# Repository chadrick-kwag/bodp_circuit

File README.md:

# bodp_circuit
battery over discharge protection circuit project.
A blog post explaining the design background and measurement procedure and results is [here](https://kwagjj.wordpress.com/2016/10/09/battery-overdischarge-protection-circuit/). Please check this post to get a glimpse of what this circuit can do.

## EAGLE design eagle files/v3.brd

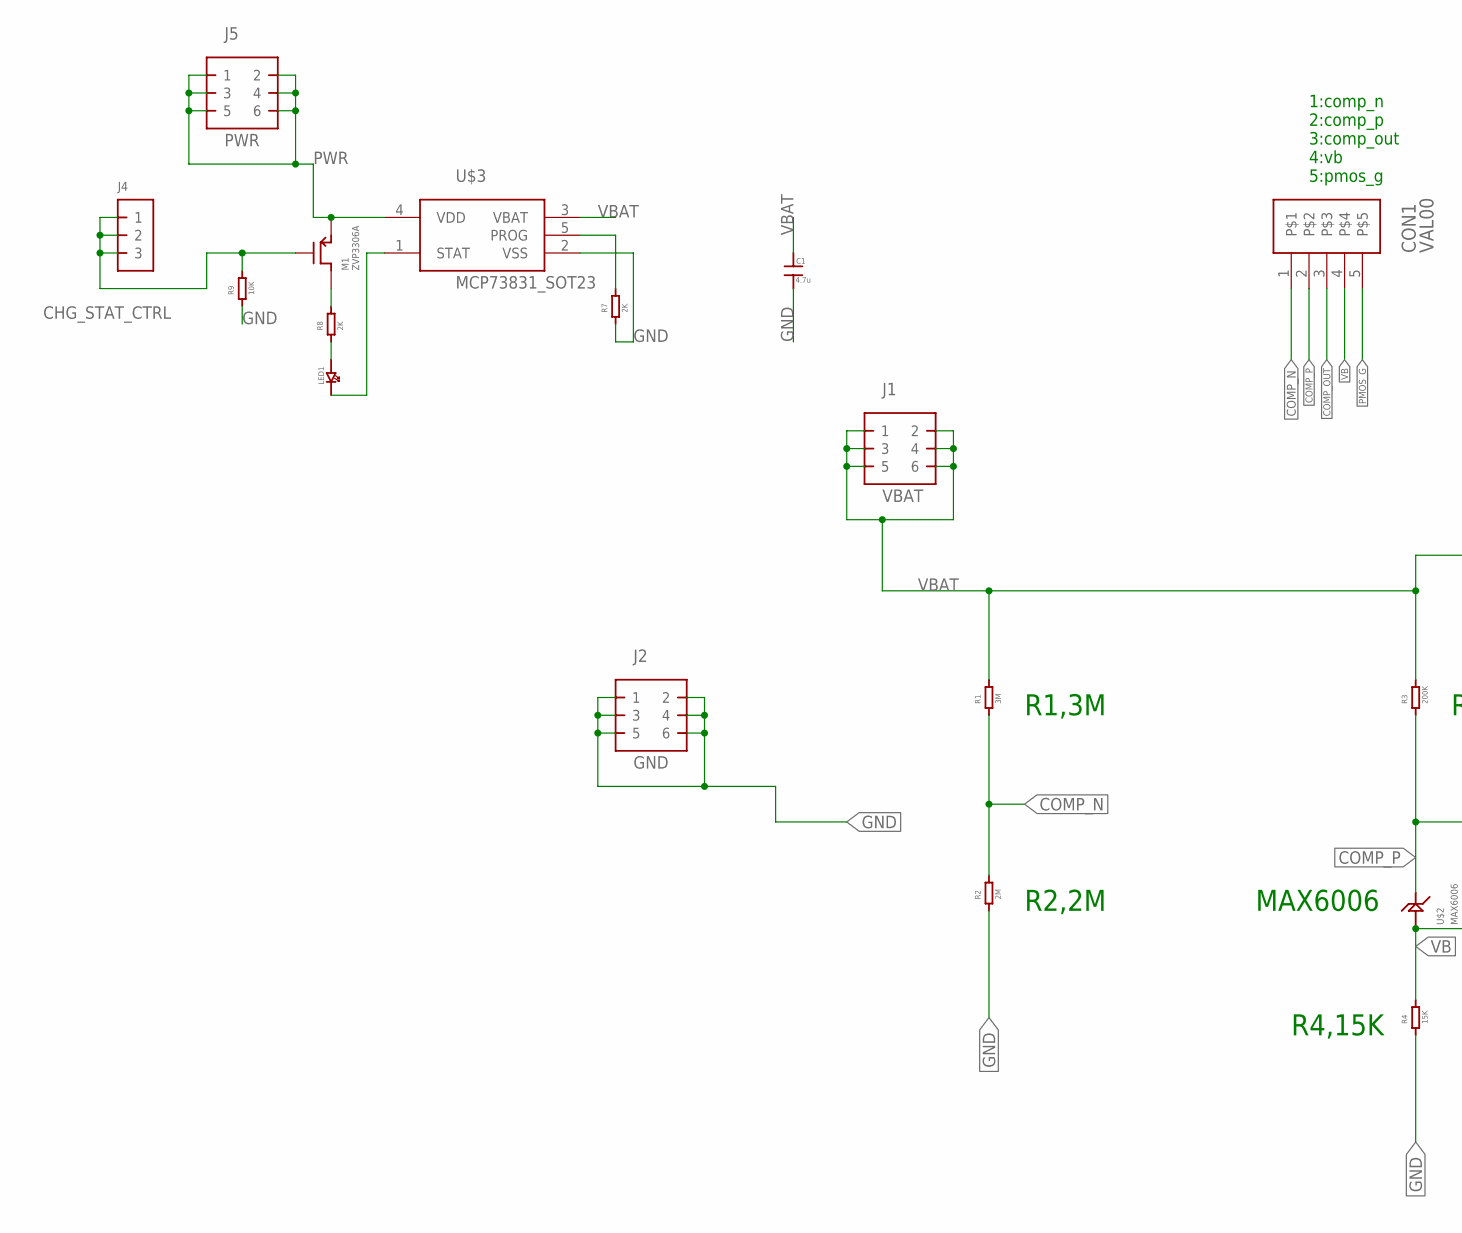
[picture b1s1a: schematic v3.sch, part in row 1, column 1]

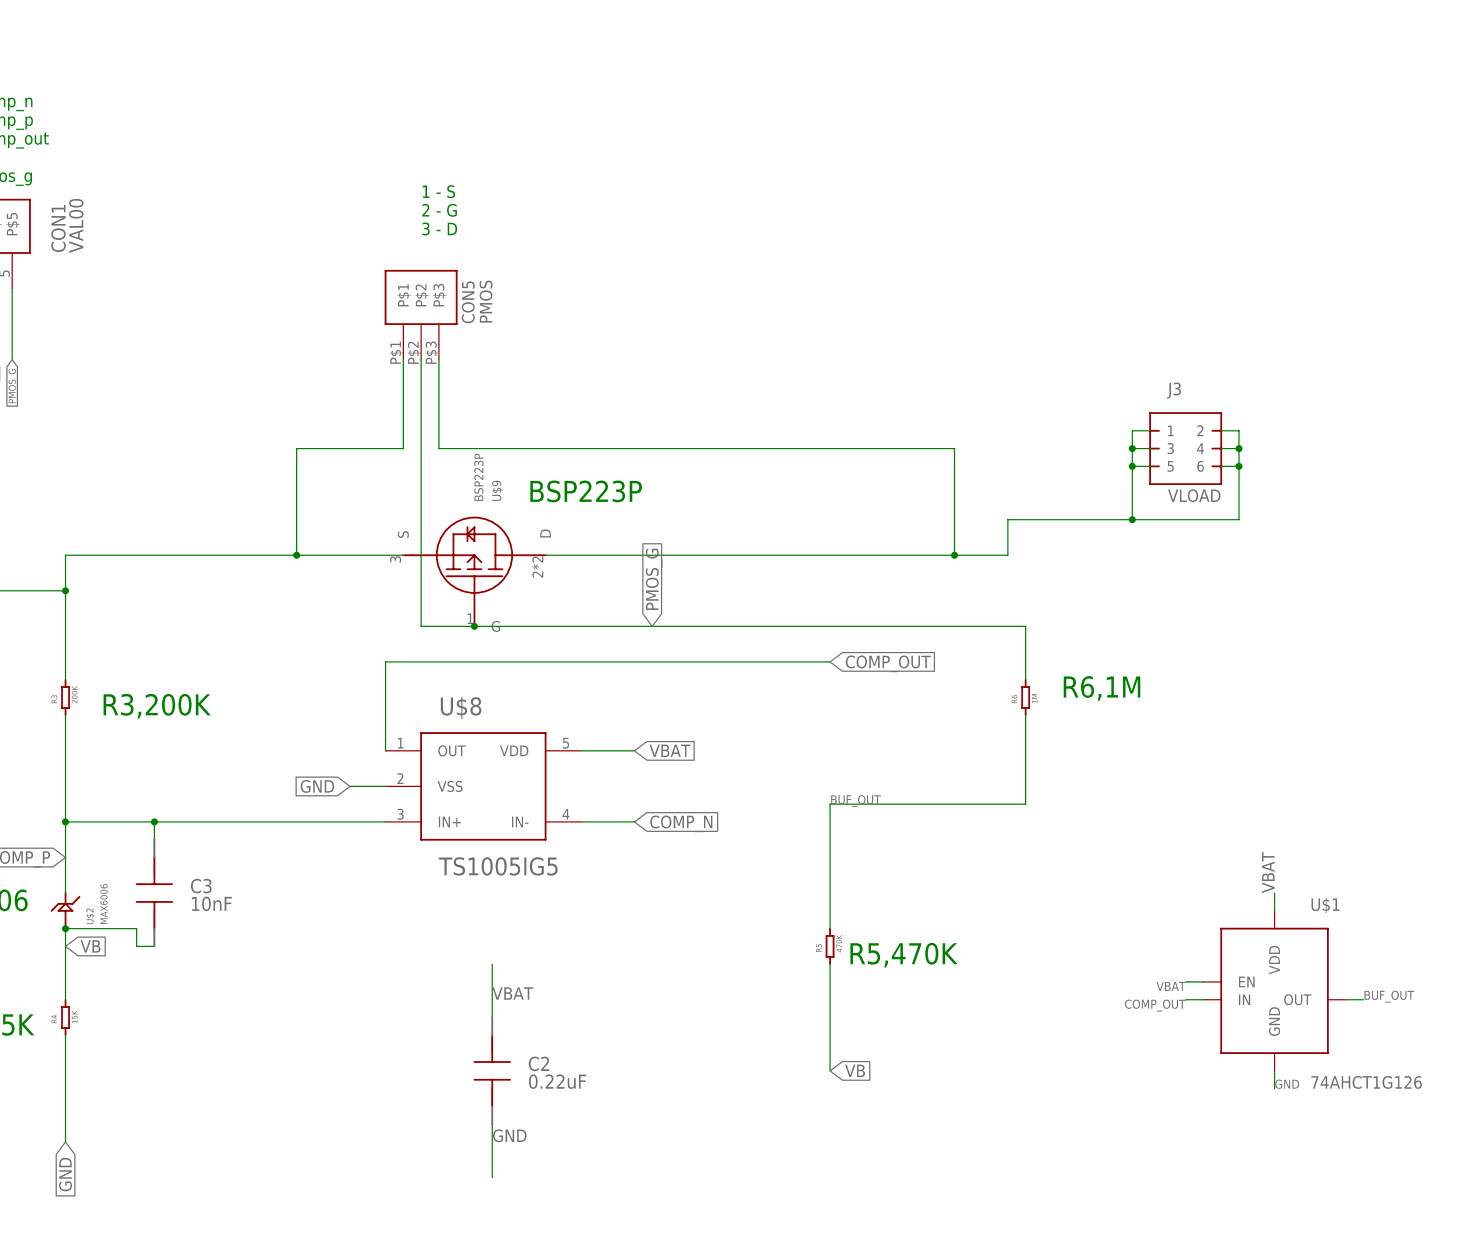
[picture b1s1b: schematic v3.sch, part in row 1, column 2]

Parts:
C1: 4.7u; GRM21
C2: 0.22uF; UMK212F224ZD-T
C3: 10nF; WALSIN_CAP_0805(2012MM)
CON1: VAL00; 1X05_PH_2.54MM
CON5: PMOS; 1X03_PH_2.54MM
J1: VBAT; 2X3_2.54MM
J2: GND; 2X3_2.54MM
J3: VLOAD; 2X3_2.54MM
J4: 1X3_2.54MM
J5: PWR; 2X3_2.54MM
LED1: LG_R971-KN-1; LG_R971-KN-1_2012
M1: ZVP3306A; ZVP3306A-TO92_2.54MM
R1: 3M; ERJ2012
R2: 2M; ERJ2012
R3: 200K; ERJ2012
R4: 15K; ERJ2012
R5: 470K; ERJ2012
R6: 1M; ERJ2012
R7, R8: 2K; ERJ2012
R9: 10K; ERJ2012
U$1: 74AHCT1G126; 74AHCT1G126-SOT353
U$2: MAX6006; 8_SO_LP_90_0096
U$3: MCP73831_SOT23; MICROCHIP-SOT-23
U$8: TS1005IG5; SILICONLABS-SOT23-5-G5_CUSTOM_V1
U$9: BSP223P; INFINION-PG-SOT-223-4N

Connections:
BUF_OUT: R5.P$1 (1), R6.P$2 (2), U$1.4 (OUT)
CHG_STAT_CTRL: J4.P$1 (1), J4.P$2 (2), J4.P$3 (3), M1.G, R9.P$1 (1)
COMP_N: CON1.1, R1.P$2 (2), R2.P$1 (1), U$8.4 (IN-)
COMP_OUT: CON1.3, U$1.2 (IN), U$8.1 (OUT)
COMP_P: C3.P$1, CON1.2, R3.P$2 (2), U$2.6 (OUT), U$2.8 (OUT), U$8.3 (IN+)
GND: C1.P$2 (2), C2.P$2, J2.P$1 (1), J2.P$2 (2), J2.P$3 (3), J2.P$4 (4), J2.P$5 (5), J2.P$6 (6), R2.P$2 (2), R4.P$2 (2), R7.P$2 (2), R9.P$2 (2), U$1.3 (GND), U$3.2 (VSS), U$8.2 (VSS)
unnamed: LED1.A (CURRENT_IN), R8.P$2 (2)
unnamed: R7.P$1 (1), U$3.5 (PROG)
unnamed: CON5.P$3, J3.P$1 (1), J3.P$2 (2), J3.P$3 (3), J3.P$4 (4), J3.P$5 (5), J3.P$6 (6), U$9.2 (D), U$9.4 (D)
unnamed: LED1.C (CURRENT_OUT), U$3.1 (STAT)
unnamed: M1.D, R8.P$1 (1)
PMOS_G: CON1.5, CON5.P$2, R6.P$1 (1), U$9.1 (G)
PWR: J5.P$1 (1), J5.P$2 (2), J5.P$3 (3), J5.P$4 (4), J5.P$5 (5), J5.P$6 (6), M1.S, U$3.4 (VDD)
VB: C3.P$2, CON1.4, R4.P$1 (1), R5.P$2 (2), U$2.4 (GND)
VBAT: C1.P$1 (1), C2.P$1, CON5.P$1, J1.P$1 (1), J1.P$2 (2), J1.P$3 (3), J1.P$4 (4), J1.P$5 (5), J1.P$6 (6), R1.P$1 (1), R3.P$1 (1), U$1.1 (EN), U$1.5 (VDD), U$3.3 (VBAT), U$8.5 (VDD), U$9.3 (S)

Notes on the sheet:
1:comp_n 2:comp_p 3:comp_out 4:vb 5:pmos_g
1 - S 2 - G 3 - D
R1,3M
R2,2M
MAX6006
R4,15K
BSP223P
R6,1M
R5,470K
R3,200K

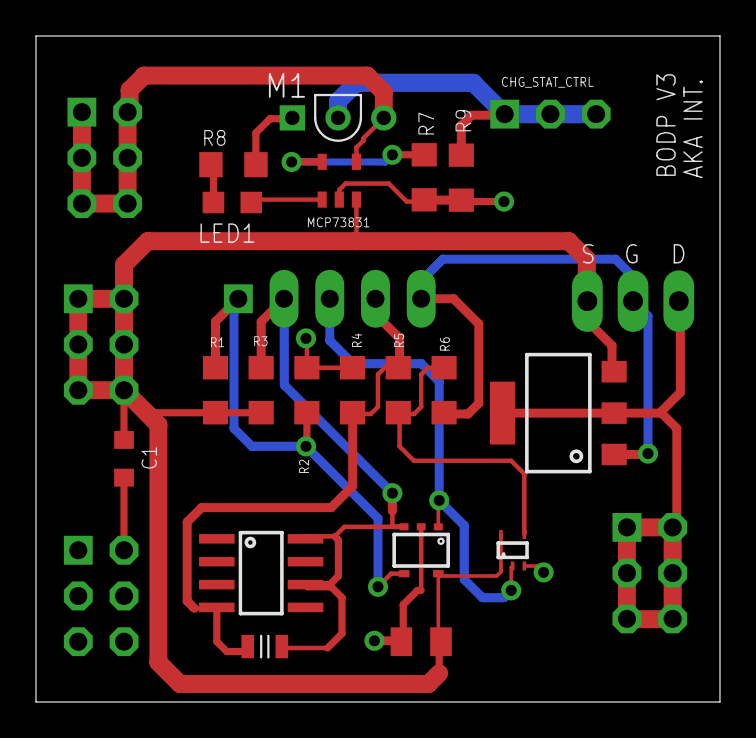
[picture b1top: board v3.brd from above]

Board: 2 copper layers, 38.0 x 37.0 mm, 26 parts (0 on the bottom side), 15 nets.

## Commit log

2016-10-09 initial add
    initial add of main files
